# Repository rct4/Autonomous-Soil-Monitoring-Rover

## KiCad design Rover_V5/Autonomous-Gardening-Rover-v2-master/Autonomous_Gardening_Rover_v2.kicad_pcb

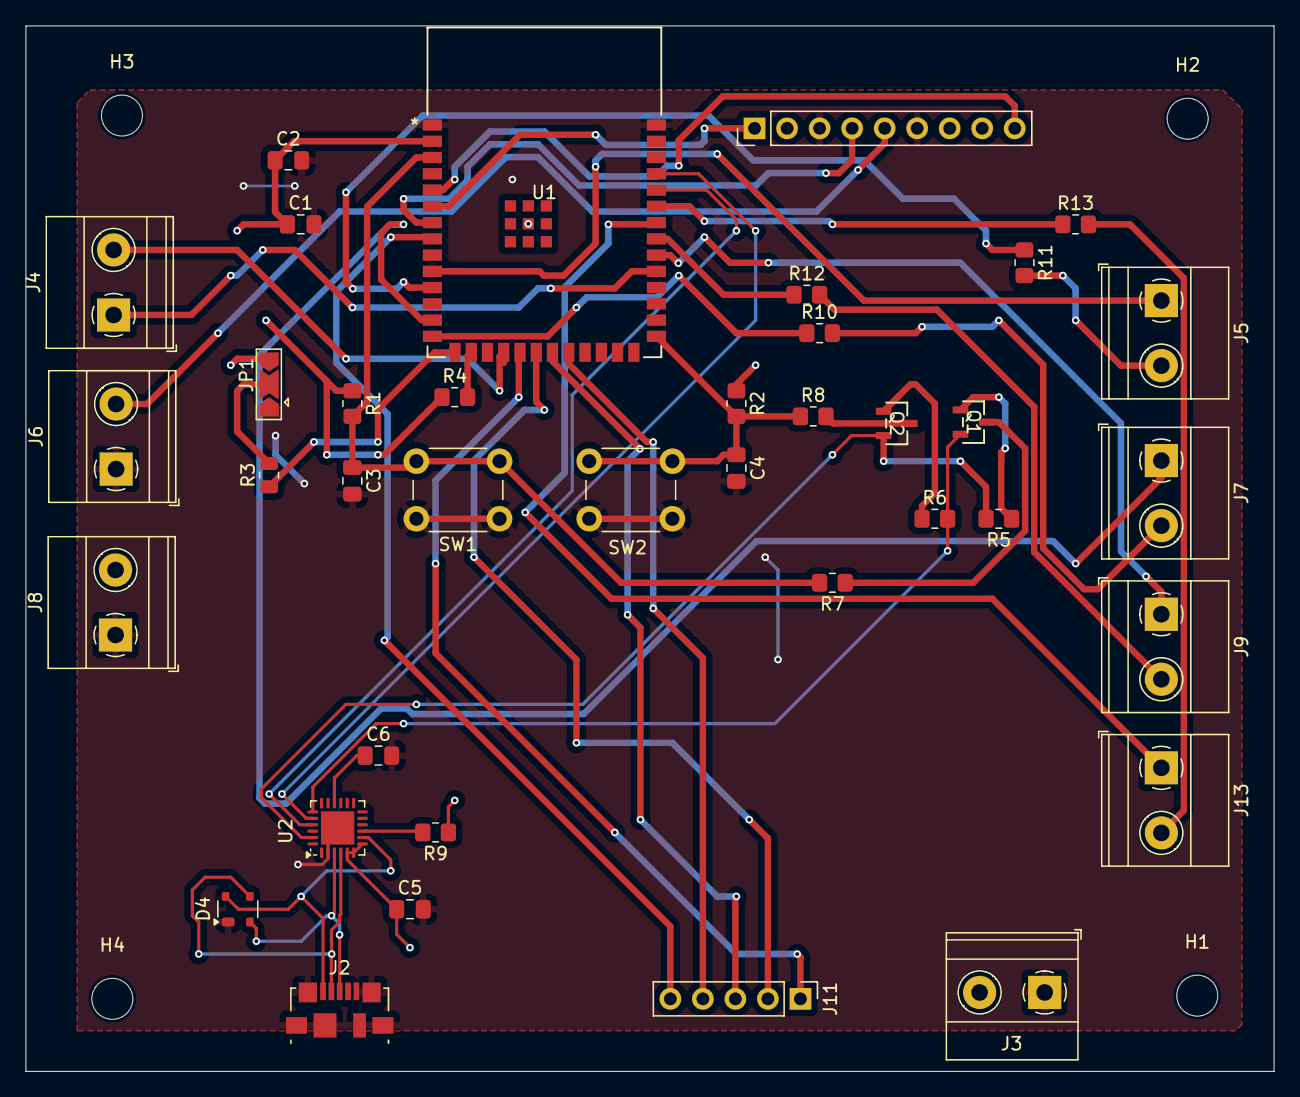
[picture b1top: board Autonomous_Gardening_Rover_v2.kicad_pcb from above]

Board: 2 copper layers, 97.5 x 81.7 mm, 42 parts (0 on the bottom side), 43 nets.

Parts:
C1: 10 uF; C_0805_2012Metric_Pad1.18x1.45mm_HandSolder
C2: 100 uF; C_0805_2012Metric_Pad1.18x1.45mm_HandSolder
C3, C4: 1 uF; C_0805_2012Metric_Pad1.18x1.45mm_HandSolder
C5: 10uF; C_0805_2012Metric_Pad1.18x1.45mm_HandSolder
C6: 4.7uF; C_0805_2012Metric_Pad1.18x1.45mm_HandSolder
D4: SP0503BAHT; SOT-143
H1, H2, H3, H4: MountingHole; MountingHole_3.2mm_M3
J2: USB_B_Micro; USB_Micro-B_Molex_47346-0001
J3: Moisture_Power; TerminalBlock_Phoenix_MKDS-1,5-2-5.08_1x02_P5.08mm_Horizont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
J4: LINEAR ACTUATOR SIGNAL; TerminalBlock_Phoenix_MKDS-1,5-2-5.08_1x02_P5.08mm_Horizont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
J5: MOTOR1SIGNAL; TerminalBlock_Phoenix_MKDS-1,5-2-5.08_1x02_P5.08mm_Horizont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
J6, J8: Screw_Terminal_01x02; TerminalBlock_Phoenix_MKDS-1,5-2-5.08_1x02_P5.08mm_Horizont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
J7: MOTOR2SIGNAL; TerminalBlock_Phoenix_MKDS-1,5-2-5.08_1x02_P5.08mm_Horizont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
J9: MOTOR3SIGNAL; TerminalBlock_Phoenix_MKDS-1,5-2-5.08_1x02_P5.08mm_Horizont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
J10: SENSORS; PinHeader_1x09_P2.54mm_Vertical
J11: UWB SIGNALS; PinHeader_1x05_P2.54mm_Vertical
J13: MOTOR4SIGNAL; TerminalBlock_Phoenix_MKDS-1,5-2-5.08_1x02_P5.08mm_Horizont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
JP1: SolderJumper_3_Open; SolderJumper-3_P2.0mm_Open_TrianglePad1.0x1.5mm
Q1, Q2: SS8050-G; TRAN_SS8050-G_CIP
R1, R2: 100k; R_0805_2012Metric_Pad1.20x1.40mm_HandSolder
R3: 1k; R_0805_2012Metric
R4: 1k; R_0805_2012Metric_Pad1.20x1.40mm_HandSolder
R5, R6, R7, R8: 10k; R_0805_2012Metric_Pad1.20x1.40mm_HandSolder
R9: 4.7k; R_0805_2012Metric_Pad1.20x1.40mm_HandSolder
R10, R11, R12, R13: 5k; R_0805_2012Metric_Pad1.20x1.40mm_HandSolder
SW1, SW2: SW_Push; SW_PUSH_6mm_H5mm
U1: ESP32-S3-WROOM-1; ESP32-S3-WROOM-1_EXP
U2: CP2104; QFN-24-1EP_4x4mm_P0.5mm_EP2.6x2.6mm

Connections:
+3V3: C1.1, C2.1, C5.1, J3.2, J8.2, J10.2, JP1.3 (B), R1.1, R2.1, R4.1, R9.1, U1.2 (3V3), U2.5 (VIO), U2.6 (VDD), U2.7 (REGIN)
+5V: J6.2, J10.5
+VBUS: D4.4 (K), J2.1 (VBUS), U2.8 (VBUS)
/CHIP_PU: C3.1, R1.2, R7.2, SW1.2, U1.3 (EN)
/D+: D4.2 (K), J2.3 (D+), U2.3 (D+)
/D-: D4.3 (K), J2.2 (D-), U2.4 (D-)
/DTR: Q2.2, R5.2, U2.23 (~DTR)
/GPIO0_STRAPPING: C4.1, R2.2, R8.1, SW2.2, U1.27 (IO0)
/GPIO3_STRAPPING: R3.1, U1.15 (IO3)
/GPIO46_STRAPPING: R4.2, U1.16 (IO46)
/LINACT+: J4.1, U1.31 (IO38)
/LINACT-: J4.2, U1.18 (IO10)
/MOTOR1FG: J5.2, R11.2
/MOTOR1PWM: J5.1, U1.10 (IO17)
/MOTOR2FG: J7.2, R10.2
/MOTOR2PWM: J7.1, U1.13 (IO19)
/MOTOR3FG: J9.2, R12.2
/MOTOR3PWM: J9.1, U1.32 (IO39)
/MOTOR4FG: J13.2, R13.2
/MOTOR4PWM: J13.1, U1.34 (IO41)
/Moisture_Sensor_Output: J10.9, U1.5 (IO5)
/RTS: Q1.2, R6.2, U2.19 (~RTS)
/RXD: U1.37 (TXD0), U2.20 (RXD)
/TXD: U1.36 (RXD0), U2.21 (TXD)
/UWBCLK: J11.2, U1.20 (IO12)
/UWBCS: J11.4, U1.22 (IO14)
/UWBINT: J11.5, U1.8 (IO15)
/UWBMISO: J11.3, U1.21 (IO13)
/UWBMOSI: J11.1, U1.19 (IO11)
/pH_Sensor: J10.1, U1.6 (IO6)
/temp_Sensor: J10.4, U1.7 (IO7)
GND: C1.2, C2.2, C3.2, C4.2, C5.2, C6.2, D4.1 (A), J2.5 (GND), J2.6 (Shield), J3.1, J6.1, J8.1, J10.3, J10.6, JP1.1 (A), SW1.1, SW2.1, U1.1 (GND), U1.40 (GND), U1.41 (GND), U2.2 (GND), U2.25 (GND)
unnamed: JP1.2 (C), R3.2
unnamed: Q1.1, R5.1
unnamed: Q1.3, R7.1
unnamed: Q2.1, R6.1
unnamed: Q2.3, R8.2
unnamed: R11.1, U1.11 (IO18)
unnamed: R10.1, U1.14 (IO20)
unnamed: R12.1, U1.33 (IO40)
unnamed: R13.1, U1.35 (IO42)
unnamed: C6.1, U2.16 (VPP)
unnamed: R9.2, U2.9 (~RST)
